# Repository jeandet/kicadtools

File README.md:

Kicad Tools
-----------

Kicad Tools is a set of tolls which aims to extend kicad functionality.

Licensing
---------

Kicad Tools is provided under the terms of the GNU General Public License as published by the
Free Software Foundation; either version 2 of the License, or (at your option) any
later version.

Wiki
----

More details  [here](https://hephaistos.lpp.polytechnique.fr/redmine/projects/kicadtools/wiki)

How to build
------------

To build it on linux you can look here https://hephaistos.lpp.polytechnique.fr/redmine/projects/kicadtools/wiki/Linux_setup

If you can't access to it, first you will need a working qt5 kit with all the development packages.
 Step 1:
  Get and install SocExplorer
```Bash
  hg clone https://hephaistos.lpp.polytechnique.fr/rhodecode/HG_REPOSITORIES/LPP/INSTRUMENTATION/kicadtools kicadtools
  cd kicadtools
  qmake-qt5
  make
  sudo make install
```

Bug repports
------------

To repport any bug you can either send a [mail](mailto:alexis.jeandet@member.fsf.org) or repport an issue [here](https://hephaistos.lpp.polytechnique.fr/redmine/projects/kicadtools/issues)

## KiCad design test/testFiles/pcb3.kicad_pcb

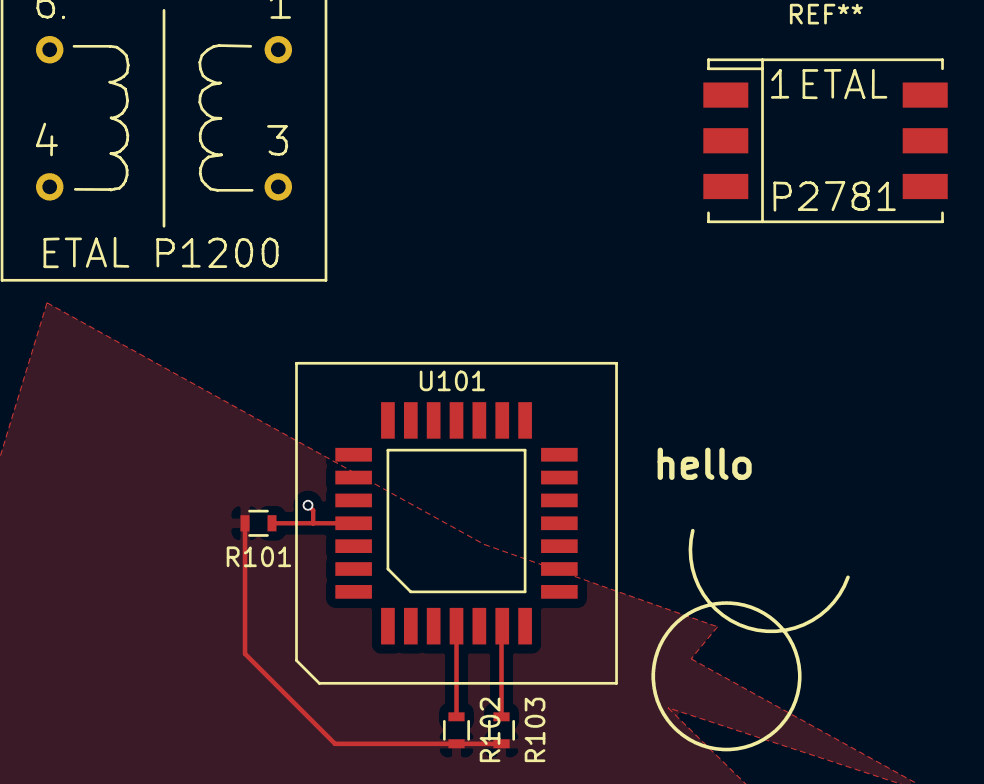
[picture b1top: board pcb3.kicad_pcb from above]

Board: 2 copper layers, 4 parts (0 on the bottom side), 4 nets.

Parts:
R101, R102, R103: R; R_0603
U101: AD390JD; PLCC-28

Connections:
unnamed: R101.1, U101.1
unnamed: R101.2, R102.2, R103.2
unnamed: R102.1, U101.8
unnamed: R103.1, U101.10

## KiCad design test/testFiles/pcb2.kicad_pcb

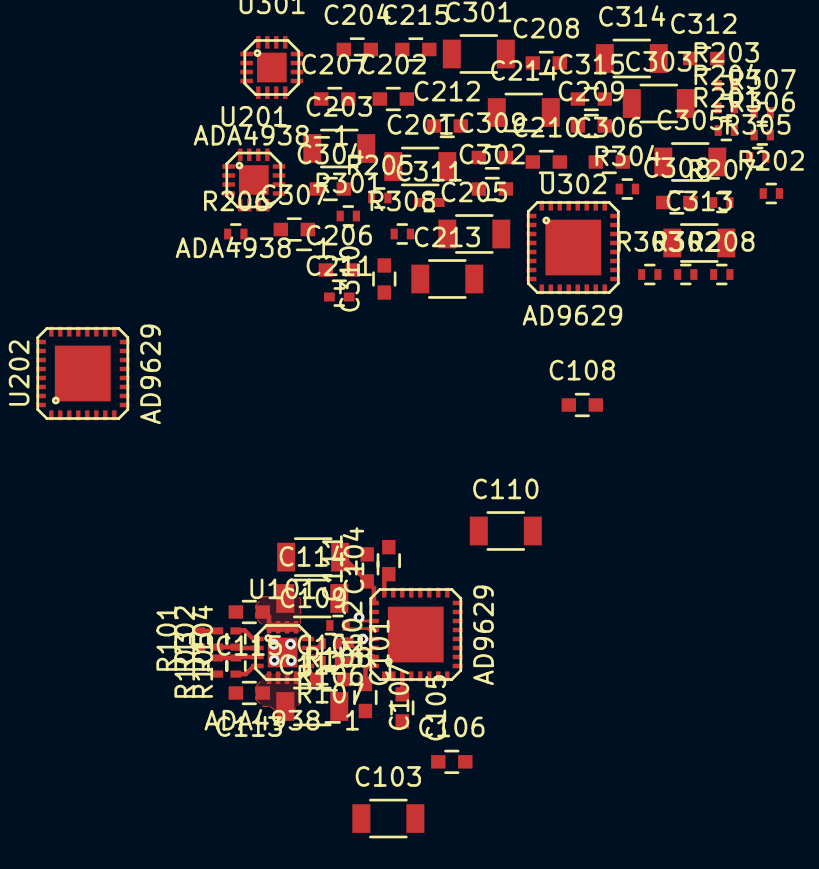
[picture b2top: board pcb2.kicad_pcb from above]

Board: 2 copper layers, 75 parts (0 on the bottom side), 49 nets.

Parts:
C101, C211, C311: 10p; C_0402
C102, C209, C309: 100nF; C_0603
C103, C109, C110, C112, C114, C201, C203, C205, C213, C214, C301, C303, C305, C313, C314: 1µ; C_1206
C104, C105, C106, C107, C108, C111, C113, C115, C202, C204, C206, C207, C208, C210, C212, C215, C302, C304, C306, C307, C308, C310, C312, C315: 100n; C_0603
R101, R201, R301: 76.8; R_0402
R102, R202, R302: 90; R_0402
R103, R203, R303: 120; R_0402
R104, R105, R204, R205, R304, R305: 200; R_0402
R106, R107, R206, R207, R306, R307: 33; R_0402
R108, R208, R308: 10k; R_0402
U101, U201, U301: ADA4938-1; LFCSP_VQ_CP16
U102, U202, U302: AD9629; LFCSP_VQ_CP32-2

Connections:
/1.8V: C103.1, C104.1, C105.1, C106.1, C107.1, U102.3, U102.24, U102.29, U102.32
/3.3V: C108.1, C110.1, U102.13
/5V: C112.1, C113.1, U101.5, U101.6, U101.7, U101.8
/-5V: C114.1, C115.1, U101.13, U101.14, U101.15, U101.16
/ADC0/1.8V: C205.1, C206.1, C207.1, C208.1, C210.1, U202.3, U202.24, U202.29, U202.32
/ADC0/3.3V: C212.1, C214.1, U202.13
/ADC0/5V: C201.1, C202.1, U201.5, U201.6, U201.7, U201.8
/ADC0/-5V: C203.1, C204.1, U201.13, U201.14, U201.15, U201.16
/ADC0/IN+: R201.2, R202.2
/ADC0/VCM: C209.1, U201.9, U202.27
/ADC0/Vref: C213.1, C215.1, U202.25
/ADC1/1.8V: C305.1, C306.1, C307.1, C308.1, C310.1, U302.3, U302.24, U302.29, U302.32
/ADC1/3.3V: C312.1, C314.1, U302.13
/ADC1/5V: C301.1, C302.1, U301.5, U301.6, U301.7, U301.8
/ADC1/-5V: C303.1, C304.1, U301.13, U301.14, U301.15, U301.16
/ADC1/IN+: R301.2, R302.2
/ADC1/VCM: C309.1, U301.9, U302.27
/ADC1/Vref: C313.1, C315.1, U302.25
/VCM: C102.1, U101.9, U102.27
/Vref: C109.1, C111.1, U102.25
GND: C102.2, C103.2, C104.2, C105.2, C106.2, C107.2, C108.2, C109.2, C110.2, C111.2, C112.2, C113.2, C114.2, C115.2, C201.2, C202.2, C203.2, C204.2, C205.2, C206.2, C207.2, C208.2, C209.2, C210.2, C212.2, C213.2, C214.2, C215.2, C301.2, C302.2, C303.2, C304.2, C305.2, C306.2, C307.2, C308.2, C309.2, C310.2, C312.2, C313.2, C314.2, C315.2, R101.1, R103.1, R108.2, R201.1, R203.1, R208.2, R301.1, R303.1, R308.2, U101.17, U102.33, U201.17, U202.33, U301.17, U302.33
unnamed: C101.1, R106.1, U102.30
unnamed: C101.2, R107.1, U102.31
unnamed: C211.1, R206.1, U202.30
unnamed: C211.2, R207.1, U202.31
unnamed: C311.1, R306.1, U302.30
unnamed: C311.2, R307.1, U302.31
unnamed: R101.2, R102.2
unnamed: R102.1, R104.1, U101.2
unnamed: R103.2, R105.2, U101.3
unnamed: R104.2, U101.1
unnamed: R105.1, U101.4
unnamed: R106.2, U101.11
unnamed: R107.2, U101.10
unnamed: R108.1, U102.28
unnamed: R202.1, R205.1, U201.2
unnamed: R203.2, R204.2, U201.3
unnamed: R204.1, U201.4
unnamed: R205.2, U201.1
unnamed: R206.2, U201.11
unnamed: R207.2, U201.10
unnamed: R208.1, U202.28
unnamed: R302.1, R305.1, U301.2
unnamed: R303.2, R304.2, U301.3
unnamed: R304.1, U301.4
unnamed: R305.2, U301.1
unnamed: R306.2, U301.11
unnamed: R307.2, U301.10
unnamed: R308.1, U302.28

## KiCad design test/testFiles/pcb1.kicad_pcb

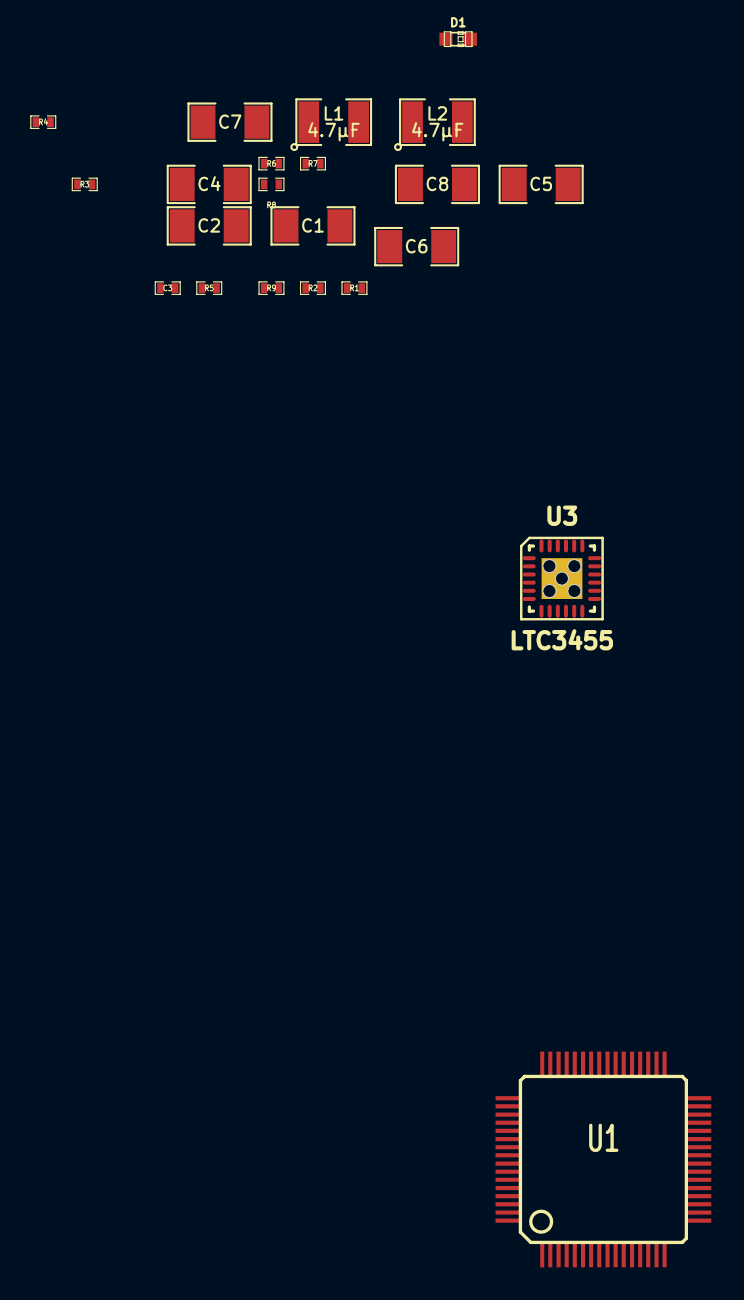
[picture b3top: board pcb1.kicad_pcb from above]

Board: 2 copper layers, 23 parts (1 on the bottom side), 16 nets, no tracks yet.

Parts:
C1, C2: 4.7µF; SM1206
C3: 100nF; SM0402
C4, C7, C8: 10µF; SM1206
C5, C6: 10pF; SM1206
D1: LED; LED-0603
L1, L2: 4.7µF; SM1210
R1: 2.49k; SM0402
R2: 2.49M; SM0402
R3: 1k; SM0402
R4: 1M; SM0402
R5: 806k; SM0402
R6: 249k; SM0402
R7: 100k; SM0402
R8, R9: 80.6k; SM0402
U1: VS1053; VQFP64
U2: TFT1P4705
U3: LTC3455; QFN24

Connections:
/power/1.8V: C6.1, C8.1, L2.2, R7.1
/power/3.3V: C5.1, C7.1, L1.2, R4.1, R6.1, U3.13
/power/I_SENS: R1.2, U3.2
/power/LOW_BAT: R4.2, U3.17
/power/VBAT: C2.1, R2.1, U3.9
/power/VBUS_USB: C1.1, D1.1, U3.8
GND: C1.2, C2.2, C3.2, C4.2, C7.2, C8.2, R1.1, R5.1, R8.2, R9.2, U3.11
unnamed: C5.2, R6.2, R8.1, U3.18
unnamed: D1.2, R3.1
unnamed: R3.2, U3.4
unnamed: C4.1, U3.10
unnamed: C6.2, R7.2, R9.1, U3.1
unnamed: L2.1, U3.7
unnamed: C3.1, U3.3
unnamed: R2.2, R5.2, U3.16
unnamed: L1.1, U3.12

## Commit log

2014-04-15 First Init, kicad lisp-like files abstract parser done.
2014-04-21 Sync
2014-04-21 Netlist parsing and loading ok, get in memory abstract syntax tree and concrete tree mapping. Next step -> PCB file parsing and loading.
2015-06-08 Some work on PCB parser.
2015-06-18 PCB Viewer is working but still WIP.
2015-06-18 Fixed some builds issues
2015-06-18 Really fixed build!
2015-06-18 Make via movable.
2015-06-19 Non working pad rendering.. Rotation issue.
2015-06-19 Fixed Pad rotation issue.
2015-06-19 Added Polygon drawing but huge perf issue, to be solved.
2015-06-21 Improved Polygon rendering by splittig them into lower complexity polygons.
2015-06-24 Improved polygon splitter and started some perf functions.
